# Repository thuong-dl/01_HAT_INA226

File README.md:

<h1 align="center">HAT_RASPI5_INA226</h1>

<p align="center" width="100%">
  
</p>

***

<p align="center">
  
&nbsp; &nbsp; &nbsp; &nbsp;
  
</p>

***

## SPECIFICATIONS

| Parameter | Value | 
| --- | --- |
| Dimensions | 38.5 × 48.5 mm |

***

## DIRECTORY STRUCTURE

    .
    ├─ Computations       # Misc calculations
    ├─ HTML               # HTML files for generated webpage
    ├─ Images             # Pictures and renders
    │
    ├─ kibot_resources    # External resources for KiBot
    │  ├─ colors          # Color theme for KiCad
    │  ├─ fonts           # Fonts used in the project
    │  ├─ scripts         # External scripts used with KiBot
    │  └─ templates       # Templates for KiBot generated reports
    │
    ├─ kibot_yaml         # KiBot YAML config files
    ├─ KiRI               # KiRI (PCB diff viewer) files
    │
    ├─ lib                # KiCad footprint and symbol libraries
    │  ├─ 3d_models       # Component 3D models
    │  ├─ lib_fp          # Footprint libraries
    │  └─ lib_sym         # Symbol libraries
    │
    ├─ Logos              # Logos
    │
    ├─ Manufacturing      # Assembly and fabrication documents
    │  ├─ Assembly        # Assembly documents (BoM, pos, notes)
    │  │
    │  └─ Fabrication     # Fabrication documents (ZIP, notes)
    │     ├─ Drill Tables # CSV drill tables
    │     └─ Gerbers      # Gerbers
    │
    ├─ Report             # Reports for ERC/DRC
    ├─ Schematic          # PDF of schematic
    ├─ Templates          # Title block templates
    ├─ Testing
    │  └─ Testpoints      # Testpoints tables      
    │
    └─ Variants           # Outputs for assembly variants

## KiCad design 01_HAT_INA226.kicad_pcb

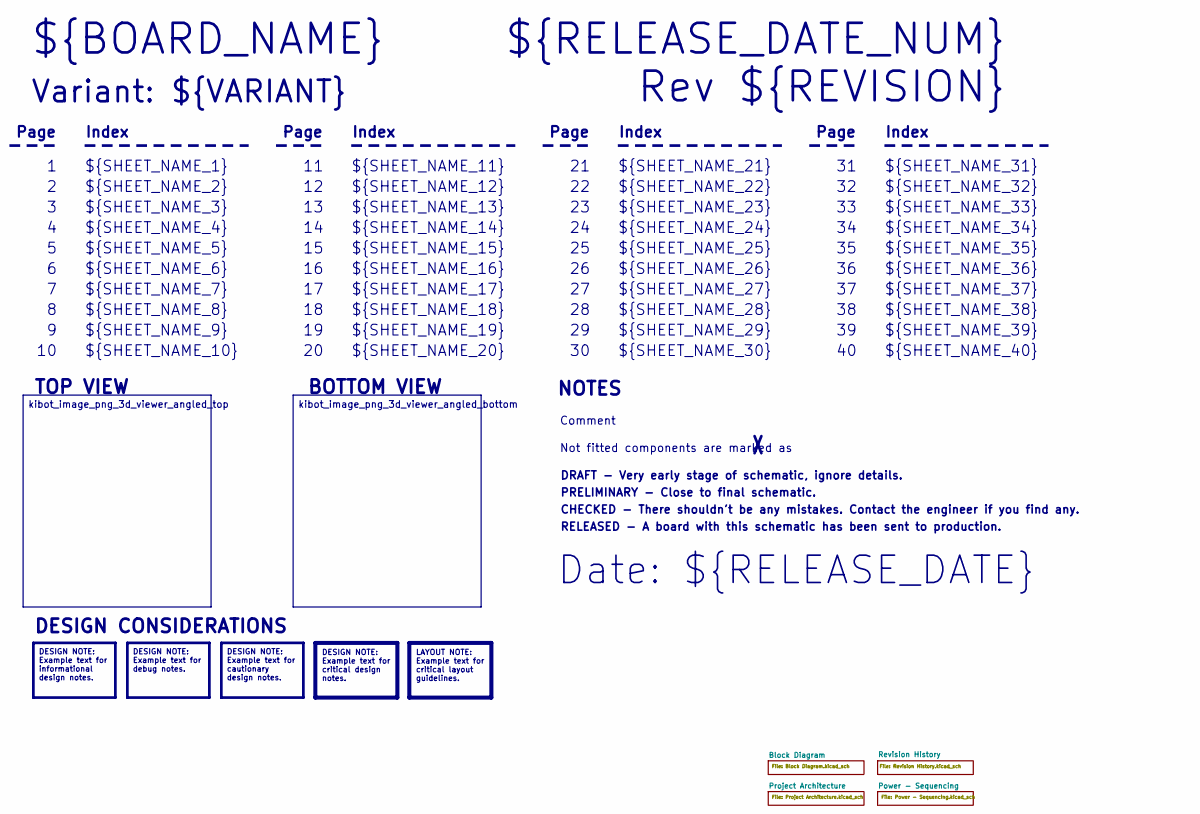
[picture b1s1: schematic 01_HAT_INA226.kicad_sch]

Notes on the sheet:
Variant: ${VARIANT}
RELEASED - A board with this schematic has been sent to production.
${SHEET_NAME_24}
Index
Page
PRELIMINARY - Close to final schematic.
${SHEET_NAME_22}
DRAFT - Very early stage of schematic, ignore details.
${SHEET_NAME_12}
${SHEET_NAME_8}
${SHEET_NAME_2}
${SHEET_NAME_5}
${SHEET_NAME_20}
${SHEET_NAME_23}
${RELEASE_DATE_NUM}
${SHEET_NAME_35}
Not fitted components are marked as
${SHEET_NAME_11}
${SHEET_NAME_6}
${SHEET_NAME_37}
${SHEET_NAME_26}
${SHEET_NAME_36}
Rev ${REVISION}
${SHEET_NAME_15}
CHECKED - There shouldn't be any mistakes. Contact the engineer if you find any.
BOTTOM VIEW
${SHEET_NAME_14}
${SHEET_NAME_21}
${SHEET_NAME_17}
${SHEET_NAME_18}
Date: ${RELEASE_DATE}
${SHEET_NAME_7}
${SHEET_NAME_31}
${BOARD_NAME}
NOTES
${SHEET_NAME_40}
${SHEET_NAME_39}
${SHEET_NAME_32}
${SHEET_NAME_1}
${SHEET_NAME_9}

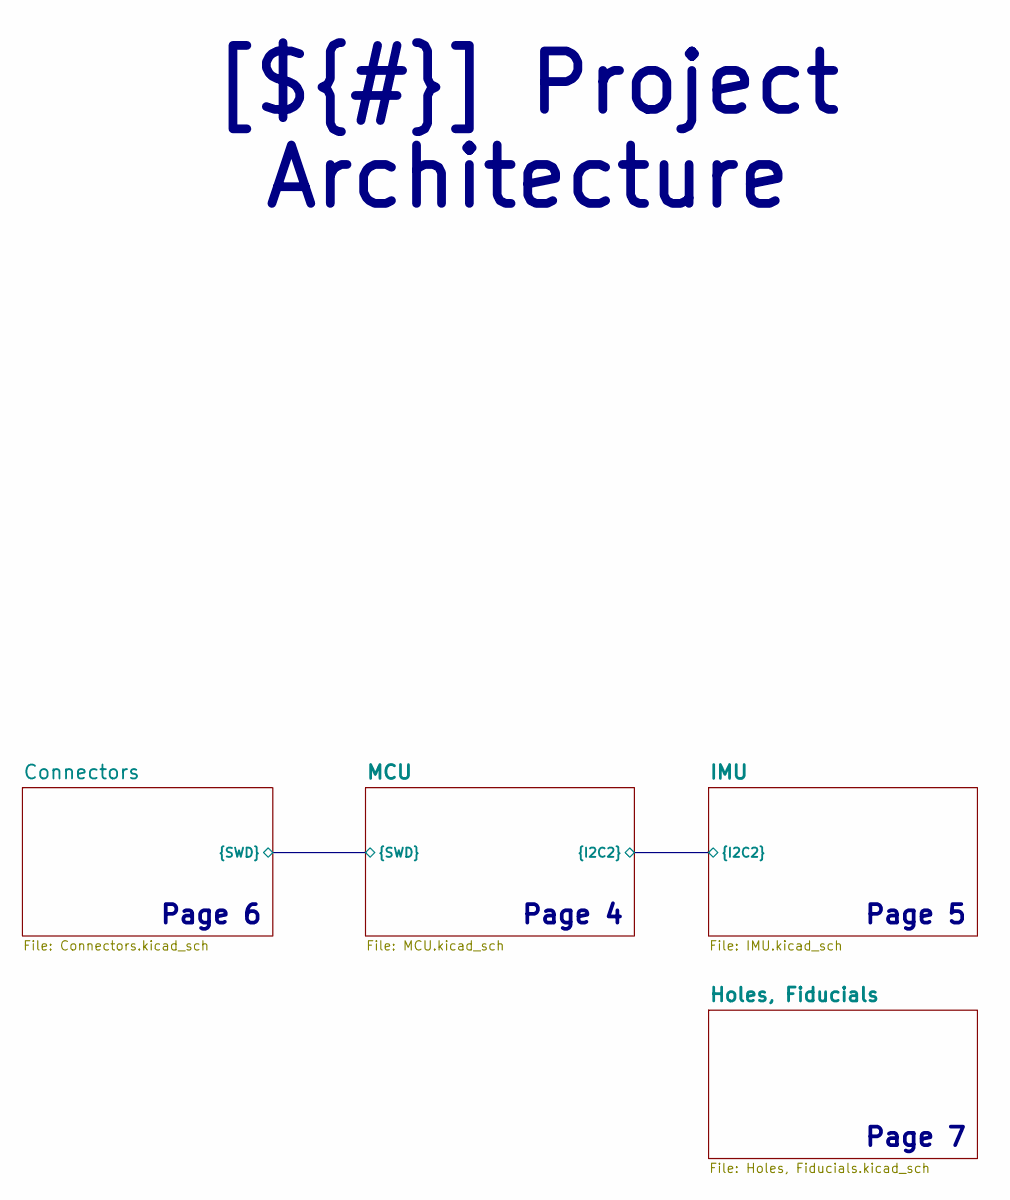
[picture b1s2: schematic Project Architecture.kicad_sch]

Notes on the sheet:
Page 4
Page 5
Page 6
Page 7
[${#}] ${TITLE}

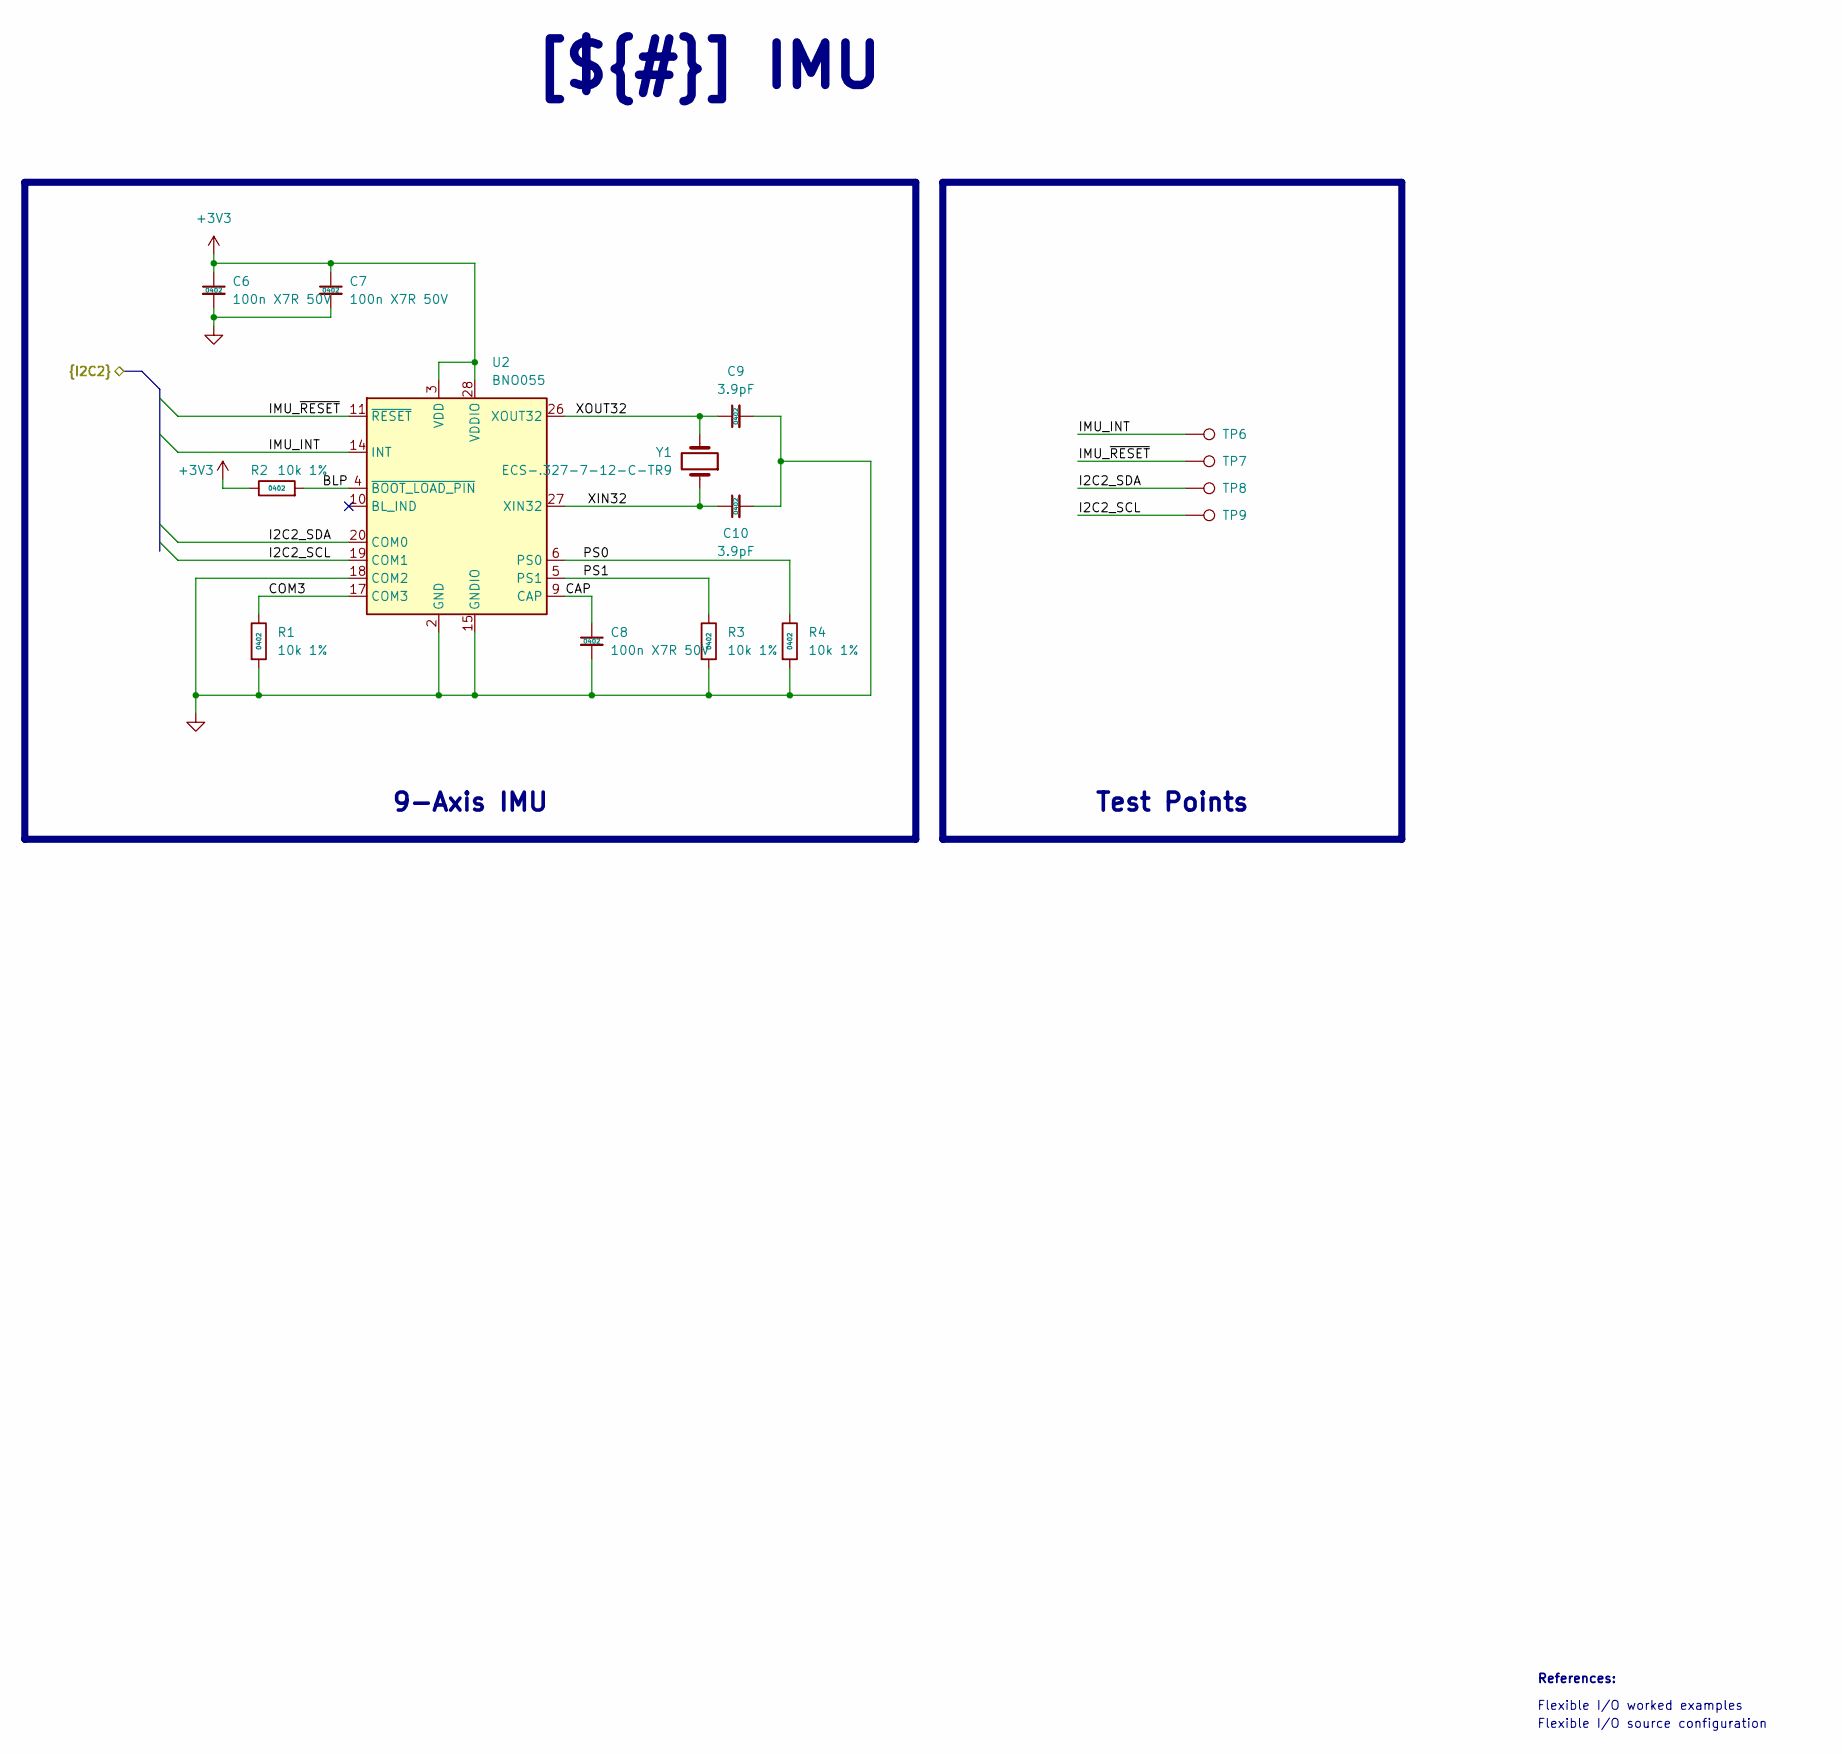
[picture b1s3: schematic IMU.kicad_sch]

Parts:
C6, C7, C8: 100n X7R 50V; C_0402_1005_DensityHigh; Manufacturer Part Number GCM155R71H104KE02J
C9, C10: 3.9pF; C_0402_1005Metric; Manufacturer Part Number 500R07S3R9BV4T
R1, R2, R3, R4: 10k 1%; R_0402_1005_DensityHigh; Manufacturer Part Number RT0402FRE0710KL
TP6, TP7, TP8, TP9: TestPoint; TestPoint_Pad_D0.5mm
U2: BNO055; LGA-28_5.2x3.8mm_P0.5mm; Manufacturer Part Number BNO055
Y1: ECS-.327-7-12-C-TR9; Crystal_SMD_2012-2Pin_2.0x1.2mm; Manufacturer Part Number ECS-.327-7-12-C-TR9

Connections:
+3V3: C6.1, C7.1, R2.1, U2.3 (VDD), U2.28 (VDDIO); also elsewhere on the board
/Project Architecture/IMU/BLP: R2.2, U2.4 (~BOOT_LOAD_PIN)
/Project Architecture/IMU/CAP: C8.1, U2.9 (CAP)
/Project Architecture/IMU/COM3: R1.1, U2.17 (COM3)
/Project Architecture/IMU/I2C2_SCL: TP9.1, U2.19 (COM1)
/Project Architecture/IMU/I2C2_SDA: TP8.1, U2.20 (COM0)
/Project Architecture/IMU/IMU_INT: TP6.1, U2.14 (INT)
/Project Architecture/IMU/IMU_~RESET: TP7.1, U2.11 (~RESET)
/Project Architecture/IMU/PS0: R4.1, U2.6 (PS0)
/Project Architecture/IMU/PS1: R3.1, U2.5 (PS1)
/Project Architecture/IMU/XIN32: C10.1, U2.27 (XIN32), Y1.1
/Project Architecture/IMU/XOUT32: C9.1, U2.26 (XOUT32), Y1.2
GND: C6.2, C7.2, C8.2, C9.2, C10.2, R1.2, R3.2, R4.2, U2.2 (GND), U2.15 (GNDIO), U2.16 (GNDIO), U2.18 (COM2), U2.25 (GNDIO); also elsewhere on the board

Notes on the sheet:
Flexible I/O worked examples
References:
Flexible I/O source configuration
[${#}] ${TITLE}
9-Axis IMU
Test Points

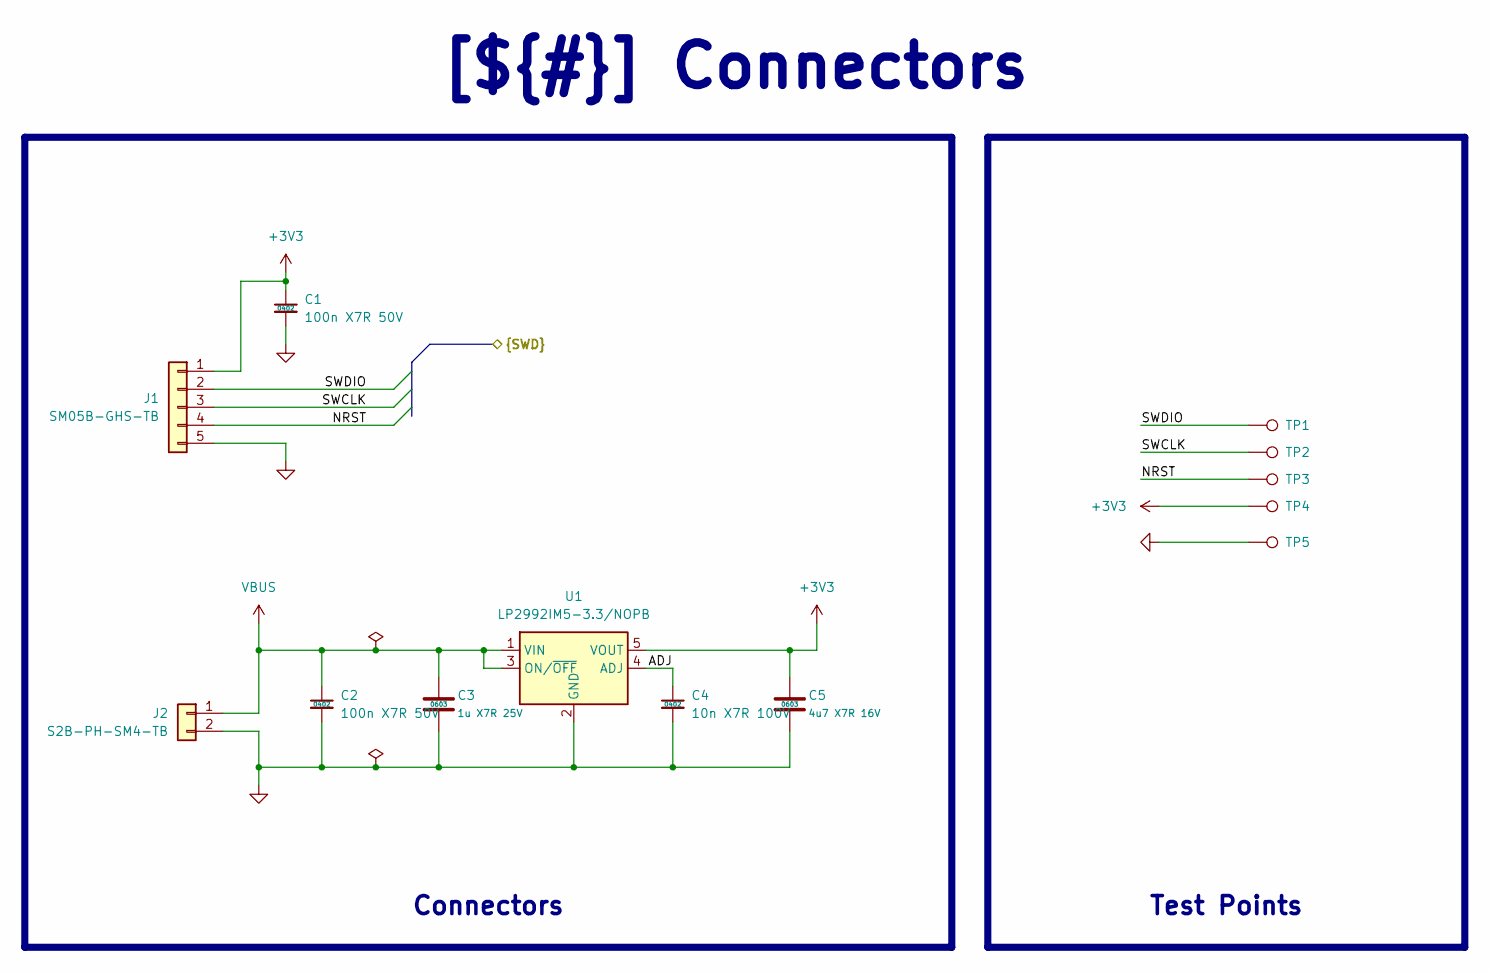
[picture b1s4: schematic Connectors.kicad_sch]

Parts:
C1, C2: 100n X7R 50V; C_0402_1005_DensityHigh; Manufacturer Part Number GCM155R71H104KE02J
C3: 1u X7R 25V; C_0603_1608_DensityHigh; Manufacturer Part Number TMK107AB7105KAHT
C4: 10n X7R 100V; C_0402_1005_DensityHigh; Manufacturer Part Number HMR105B7103KV-F
C5: 4u7 X7R 16V; C_0603_1608_DensityHigh; Manufacturer Part Number GRM188Z71C475KE21J
J1: SM05B-GHS-TB; JST_GH_SM05B-GHS-TB_1x05-1MP_P1.25mm_Horizontal; Manufacturer Part Number SM05B-GHS-TB
J2: S2B-PH-SM4-TB; JST_PH_S2B-PH-SM4-TB_1x02-1MP_P2.00mm_Horizontal; Manufacturer Part Number S2B-PH-SM4-TB
TP1, TP2, TP3, TP4, TP5: TestPoint; TestPoint_Pad_D0.5mm
U1: LP2992IM5-3.3/NOPB; SOT-23-5; Manufacturer Part Number LP2992IM5-3.3/NOPB

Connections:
+3V3: C1.1, C5.1, J1.1, TP4.1, U1.5 (VOUT); also elsewhere on the board
/Project Architecture/Connectors/ADJ: C4.1, U1.4 (ADJ)
/Project Architecture/Connectors/NRST: J1.4, TP3.1
/Project Architecture/Connectors/SWCLK: J1.3, TP2.1
/Project Architecture/Connectors/SWDIO: J1.2, TP1.1
GND: C1.2, C2.2, C3.2, C4.2, C5.2, J1.5, J2.2, TP5.1, U1.2 (GND); also elsewhere on the board
VBUS: C2.1, C3.1, J2.1, U1.1 (VIN), U1.3 (ON/~OFF)

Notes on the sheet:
Connectors
[${#}] ${TITLE}
Test Points

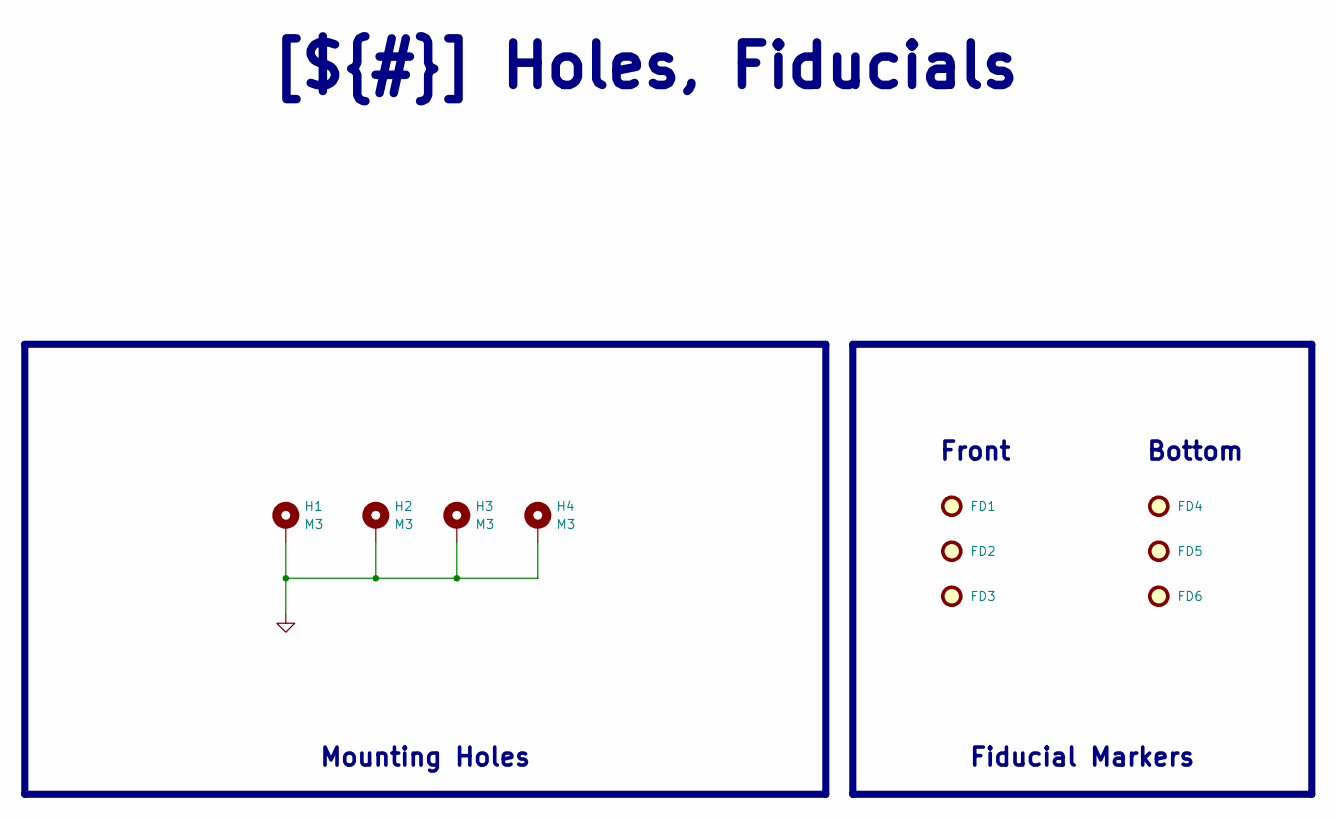
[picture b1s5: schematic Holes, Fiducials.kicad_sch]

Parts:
FD1, FD2, FD3, FD4, FD5, FD6: Fiducial; Fiducial_1mm_Mask2mm
H1, H2, H3, H4: M3; MountingHole_3.2mm_M3_Pad

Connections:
GND: H1.1, H2.1, H3.1, H4.1; also elsewhere on the board

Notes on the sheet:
[${#}] ${TITLE}
Front
Bottom
Mounting Holes
Fiducial Markers

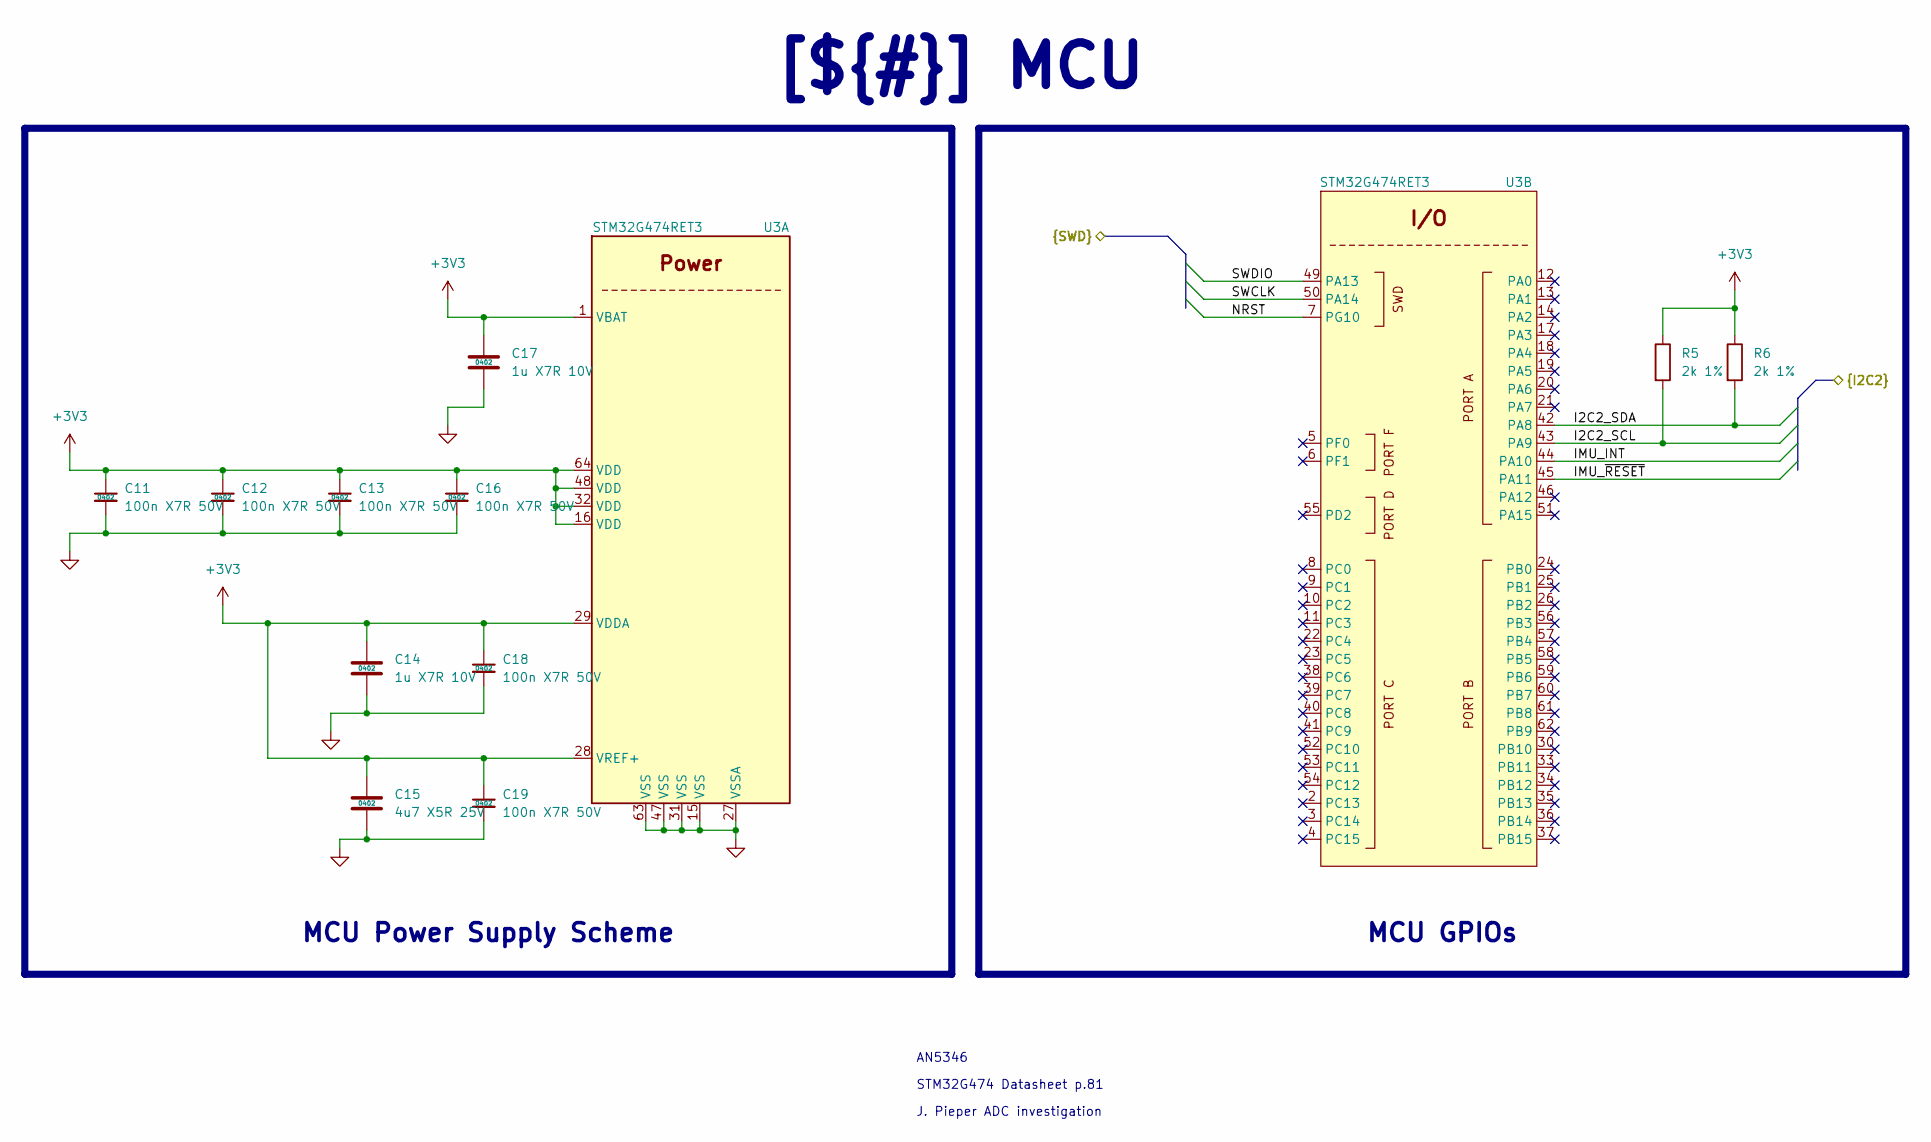
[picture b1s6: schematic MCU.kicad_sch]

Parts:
C11, C12, C13, C16, C18, C19: 100n X7R 50V; C_0402_1005_DensityHigh; Manufacturer Part Number GCM155R71H104KE02J
C14, C17: 1u X7R 10V; C_0402_1005_DensityHigh; Manufacturer Part Number GRM155Z71A105KE01J
C15: 4u7 X5R 25V; C_0402_1005_DensityHigh; Manufacturer Part Number CM05X5R475M25AH
R5, R6: 2k 1%; R_0402_1005_DensityHigh; Manufacturer Part Number ERJ-2RKF2001X
U3: STM32G474RET3; LQFP-64_10x10mm_P0.5mm; Manufacturer Part Number STM32G474RET3

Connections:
+3V3: C11.1, C12.1, C13.1, C14.1, C15.1, C16.1, C17.1, C18.1, C19.1, R5.1, R6.1, U3.1 (VBAT), U3.16 (VDD), U3.28 (VREF+), U3.29 (VDDA), U3.32 (VDD), U3.48 (VDD), U3.64 (VDD); also elsewhere on the board
/Project Architecture/MCU/I2C2_SCL: R5.2, U3.43 (PA9)
/Project Architecture/MCU/I2C2_SDA: R6.2, U3.42 (PA8)
/Project Architecture/MCU/IMU_INT: U3.44 (PA10)
/Project Architecture/MCU/IMU_~RESET: U3.45 (PA11)
/Project Architecture/MCU/NRST: U3.7 (PG10)
/Project Architecture/MCU/SWCLK: U3.50 (PA14)
/Project Architecture/MCU/SWDIO: U3.49 (PA13)
GND: C11.2, C12.2, C13.2, C14.2, C15.2, C16.2, C17.2, C18.2, C19.2, U3.15 (VSS), U3.27 (VSSA), U3.31 (VSS), U3.47 (VSS), U3.63 (VSS); also elsewhere on the board

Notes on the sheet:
J. Pieper ADC investigation
STM32G474 Datasheet p.81
AN5346
MCU GPIOs
[${#}] ${TITLE}
MCU Power Supply Scheme

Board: 6 copper layers, 50 parts (0 on the bottom side), 20 nets, no tracks yet.

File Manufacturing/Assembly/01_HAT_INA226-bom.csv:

Row,Quantity Per PCB,References,Value,Datasheet,Footprint,Description,Manufacturer,Manufacturer Part Number,Supplier Part Number
1,2,C9 C10,3.9pF,https://www.johansontechnology.com/downloads/catalog/johanso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,C_0402_1005Metric,"3.9 pF ±0.1pF 50V Ceramic Capacitor C0G, NP0 0402 (1005 Metric)",Johanson Technology Inc.,500R07S3R9BV4T,
2,1,C4,10n X7R 100V,https://mm.digikey.com/Volume0/opasdata/d220001/medias/docus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,C_0402_1005_DensityHigh,10000 pF ±10% 100V Ceramic Capacitor X7R 0402 (1005 Metric),Taiyo Yuden,HMR105B7103KV-F,
3,11,C1 C2 C6 C7 C8 C11 C12 C13 C16 C18 C19,100n X7R 50V,https://search.murata.co.jp/Ceramy/image/img/A01X/G101/ENG/G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,C_0402_1005_DensityHigh,0.1 µF ±10% 50V Ceramic Capacitor X7R 0402 (1005 Metric),Murata Electronics,GCM155R71H104KE02J,
4,2,C14 C17,1u X7R 10V,https://search.murata.co.jp/Ceramy/image/img/A01X/G101/ENG/G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,C_0402_1005_DensityHigh,1 µF ±10% 10V Ceramic Capacitor X7R 0402 (1005 Metric),Murata Electronics,GRM155Z71A105KE01J,
5,1,C3,1u X7R 25V,https://mm.digikey.com/Volume0/opasdata/d220001/medias/docus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,C_0603_1608_DensityHigh,1 µF ±10% 25V Ceramic Capacitor X7R 0603 (1608 Metric),Taiyo Yuden,TMK107AB7105KAHT,
6,1,C15,4u7 X5R 25V,https://www.mouser.ch/datasheet/2/40/CM_Series_e-2835982.pdf,C_0402_1005_DensityHigh,4.7 µF ±20% 25V Ceramic Capacitor X5R 0402 (1005 Metric),KYOCERA AVX,CM05X5R475M25AH,
7,1,C5,4u7 X7R 16V,https://search.murata.co.jp/Ceramy/image/img/A01X/G101/ENG/G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,C_0603_1608_DensityHigh,4.7 µF ±10% 16V Ceramic Capacitor X7R 0603 (1608 Metric),Murata Electronics,GRM188Z71C475KE21J,
8,1,J2,S2B-PH-SM4-TB,https://www.jst-mfg.com/product/pdf/eng/ePH.pdf,JST_PH_S2B-PH-SM4-TB_1x02-1MP_P2.00mm_Horizontal,https://www.jst-mfg.com/product/pdf/eng/ePH.pdf,JST Sales America Inc.,S2B-PH-SM4-TB,
9,1,J1,SM05B-GHS-TB,https://www.jst-mfg.com/product/pdf/eng/eGH.pdf,JST_GH_SM05B-GHS-TB_1x05-1MP_P1.25mm_Horizontal,"Connector Header Surface Mount, Right Angle 5 position 0.049"" (1.25mm)",JST Sales America Inc.,SM05B-GHS-TB,
10,2,R5 R6,2k 1%,https://industrial.panasonic.com/cdbs/www-data/pdf/RDA0000/A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,R_0402_1005_DensityHigh,"2 kOhms ±1% 0.1W, 1/10W Chip Resistor 0402 (1005 Metric) Automotive AEC-Q200 Thick Film",Vishay,ERJ-2RKF2001X,
11,4,R1 R2 R3 R4,10k 1%,https://www.yageo.com/upload/media/product/app/datasheet/rch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,R_0402_1005_DensityHigh,"10 kOhms ±1% 0.063W, 1/16W Chip Resistor 0402 (1005 Metric) Thin Film",YAGEO,RT0402FRE0710KL,
12,1,U2,BNO055,https://www.bosch-sensortec.com/media/boschsensortec/downloa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,LGA-28_5.2x3.8mm_P0.5mm,"Intelligent 9-axis absolute orientation sensor, LGA-28",Bosch Sensortec,BNO055,
13,1,U1,LP2992IM5-3.3/NOPB,https://www.ti.com/lit/ds/symlink/lp2992.pdf,SOT-23-5,Micropower 250-mA Low-Noise Ultra-Low-Dropout Regulator,Texas Instruments,LP2992IM5-3.3/NOPB,
14,1,U3,STM32G474RET3,https://www.st.com/resource/en/datasheet/stm32g474re.pdf,LQFP-64_10x10mm_P0.5mm,"STMicroelectronics Arm Cortex-M4 MCU, 512KB flash, 128KB RAM, 170 MHz, 1.71-3.6V, 58 GPIO, LQFP64",STMicroelectronics,STM32G474RET3,
15,1,Y1,ECS-.327-7-12-C-TR9,https://ecsxtal.com/store/pdf/ECX_12.pdf,Crystal_SMD_2012-2Pin_2.0x1.2mm,"32.768 kHz ±10ppm Crystal 7pF 90 kOhms 2-SMD, No Lead",ECS Inc.,ECS-.327-7-12-C-TR9,
